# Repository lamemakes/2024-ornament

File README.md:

# ✨ Blinky Tree ✨

**A super simple holiday ornament that whimsically blinks some LEDs**

## How's it work?

This utilizes [charlieplexing](https://en.wikipedia.org/wiki/Charlieplexing) & an ATTiny85 to control 12 LEDs. When it isn't flashing it's LEDs due to a button trigger, the ATTiny is in a state of [deep sleep ](https://onlinedocs.microchip.com/oxy/GUID-317042D4-BCCE-4065-BB05-AC4312DBC2C4-en-US-2/GUID-0EC704BC-648F-4BF6-90AE-0FAF9C596013.html) and thus using very little power, which is why it can be powered with a CR2032.

## Pics

*Schematic*

*PCB*

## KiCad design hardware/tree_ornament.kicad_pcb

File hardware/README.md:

# ⚙️ Blinky Tree Hardware

## BOM

| Part No.         | Link                                                                                            | Quantity | Notes                     | 
|------------------|-------------------------------------------------------------------------------------------------|----------|---------------------------|
| BC-2003-FH-TR    | https://www.digikey.com/en/products/detail/mpd-memory-protection-devices/BC-2003-FH-TR/16692312 | 1        | CR2032 Battery Holder     |
| 151031VS06000    | https://www.digikey.com/en/products/detail/w%C3%BCrth-elektronik/151031VS06000/4489988          | 6        | Green LED                 |
| 151031SS06000    | https://www.digikey.com/en/products/detail/w%C3%BCrth-elektronik/151031SS06000/4489982          | 6        | Red LED                   |
| TL1107BF130WQ    | https://www.digikey.com/en/products/detail/e-switch/TL1107BF130WQ/378978                        | 1        | Button                    |
| ATTINY85-20PU-ND | https://www.digikey.com/en/products/detail/microchip-technology/ATTINY85-20PU/735469            | 1        | "Brains" of the operation |
| CF18JT200R       | https://www.digikey.com/en/products/detail/stackpole-electronics-inc/CF18JT200R/1741632         | 4        | 200Ω Resistor             |
| CF18JT10K0       | https://www.digikey.com/en/products/detail/stackpole-electronics-inc/cf18jt10k0/1741566         | 1        | 10kΩ Resistor             |

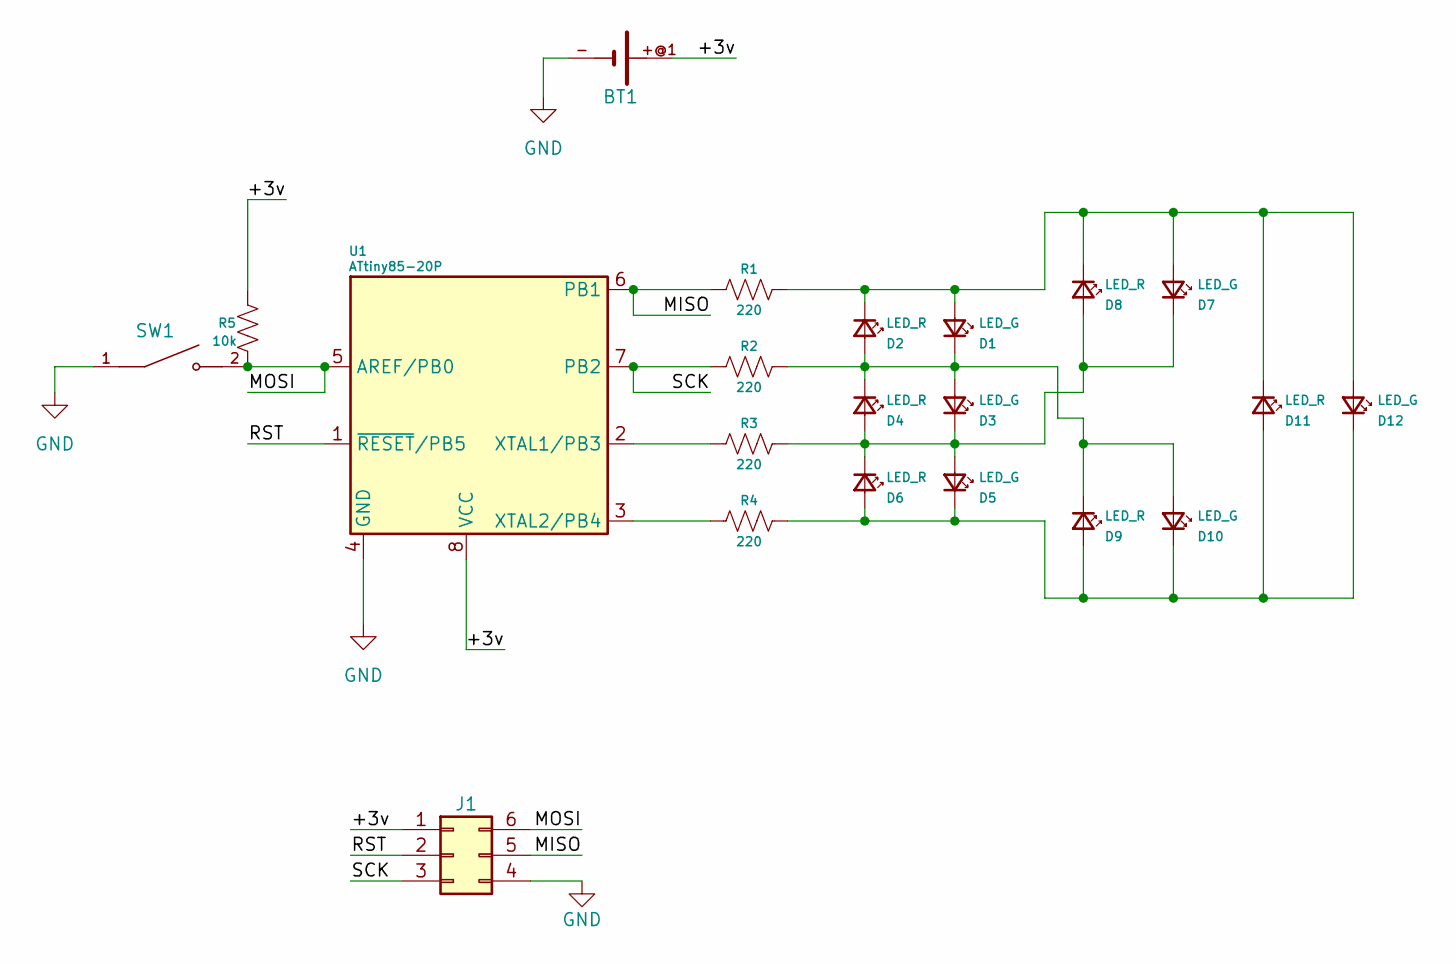
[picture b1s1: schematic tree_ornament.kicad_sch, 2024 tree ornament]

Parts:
BT1: 3002; BAT_3002
D1, D3, D5, D7, D10, D12: LED_G; WL-TMRC_3MM_LED
D2, D4, D6, D8, D9, D11: LED_R; WL-TMRC_3MM_LED
J1: Conn_02x03_Counter_Clockwise; PinHeader_2x03_P2.54mm_Vertical
R1, R2, R3, R4: 220; R_Axial_DIN0204_L3.6mm_D1.6mm_P7.62mm_Horizontal
R5: 10k; R_Axial_DIN0204_L3.6mm_D1.6mm_P7.62mm_Horizontal
SW1: TL1107BF130WQ; SW_TL1107BF130WQ
U1: ATtiny85-20P; SOIC127P798X216-8N

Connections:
/+3v: BT1.+@1, J1.1, R5.1, U1.8 (VCC)
/MISO: J1.5, R1.2, U1.6 (PB1)
/MOSI: J1.6, R5.2, SW1.2, U1.5 (AREF/PB0)
/RST: J1.2, U1.1 (~RESET/PB5)
/SCK: J1.3, R2.2, U1.7 (PB2)
GND: BT1.-, J1.4, SW1.1, U1.4 (GND)
unnamed: D1.1 (A), D2.2 (K), D7.1 (A), D8.2 (K), D11.2 (K), D12.1 (A), R1.1
unnamed: D1.2 (K), D2.1 (A), D3.1 (A), D4.2 (K), D9.2 (K), D10.1 (A), R2.1
unnamed: D3.2 (K), D4.1 (A), D5.1 (A), D6.2 (K), D7.2 (K), D8.1 (A), R3.1
unnamed: D5.2 (K), D6.1 (A), D9.1 (A), D10.2 (K), D11.1 (A), D12.2 (K), R4.1
unnamed: R3.2, U1.2 (XTAL1/PB3)
unnamed: R4.2, U1.3 (XTAL2/PB4)

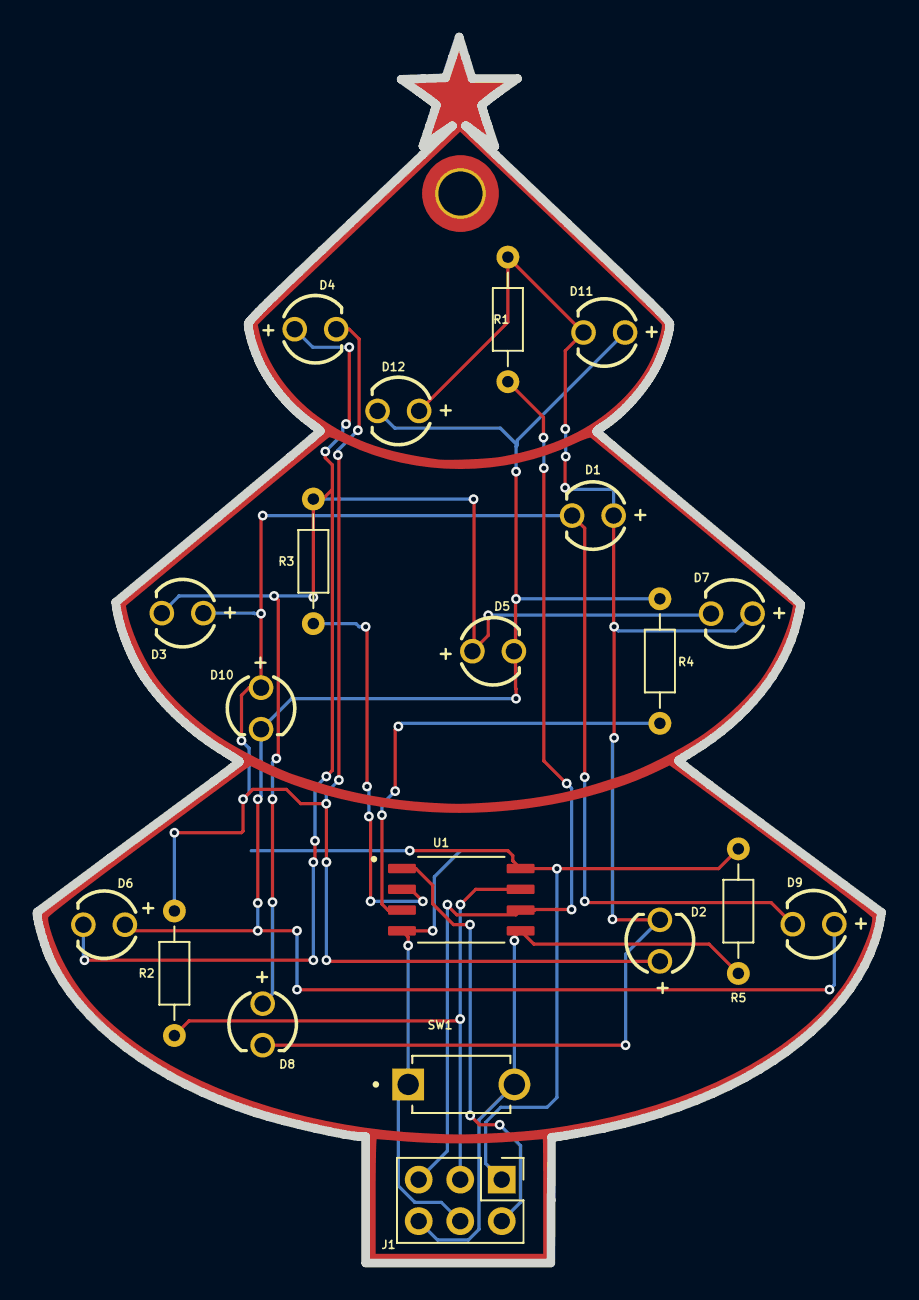
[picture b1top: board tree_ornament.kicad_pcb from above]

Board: 2 copper layers, 51.7 x 75.0 mm, 21 parts (1 on the bottom side), 12 nets.

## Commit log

2024-11-23 Added licenses & more README content
2024-11-28 Added silkscreen/edge cuts, placed footprints, initial release
2024-11-28 Added github workflow
2024-11-28 Actions commit update
2024-11-28 Actions path update
2024-11-29 Actions path updates
2024-11-29 fixed project name
2024-11-29 Update KiCad Image
2024-12-02 README updates, action commit updated
2024-12-02 Updated README to include generated pics
2024-12-08 Found unconnected LEDs, cleaned up firmware code
2024-12-10 Fixed swapped pins
